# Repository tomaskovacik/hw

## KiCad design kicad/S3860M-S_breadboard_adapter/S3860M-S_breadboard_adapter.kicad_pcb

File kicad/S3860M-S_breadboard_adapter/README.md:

breadboard adapter for the S3860M-S module (check markings on your module, this is not for the XS3868 module, nor BLK module!)
 
What's new in version 2.0:

buttons: on/off, reset, next, previous, volume up and down

jack: output (optional over 1206 caps (by default this is bypassed by PCB trace, so trace need to be cut for caps to work), mono mic + all required bias circuit

12+12pin headers

breadboard adapters for these bluetooth modules can be purchase at Tindie.com :

BLK-MD-SPK-B https://www.tindie.com/products/tomaskovacik/breadboard-adapter-for-blk-md-spk-b/

XS3886 / S3860M-s https://www.tindie.com/products/tomaskovacik/breadboard-adapter-for-s3860m-s-sx3868/

SOYO-BT24G03 https://www.tindie.com/products/tomaskovacik/breadboard-adapter-for-soyo-bt24g03-bt-module/

F-3188 https://www.tindie.com/products/tomaskovacik/breadboard-adapter-for-f-3188-csr8645-module/

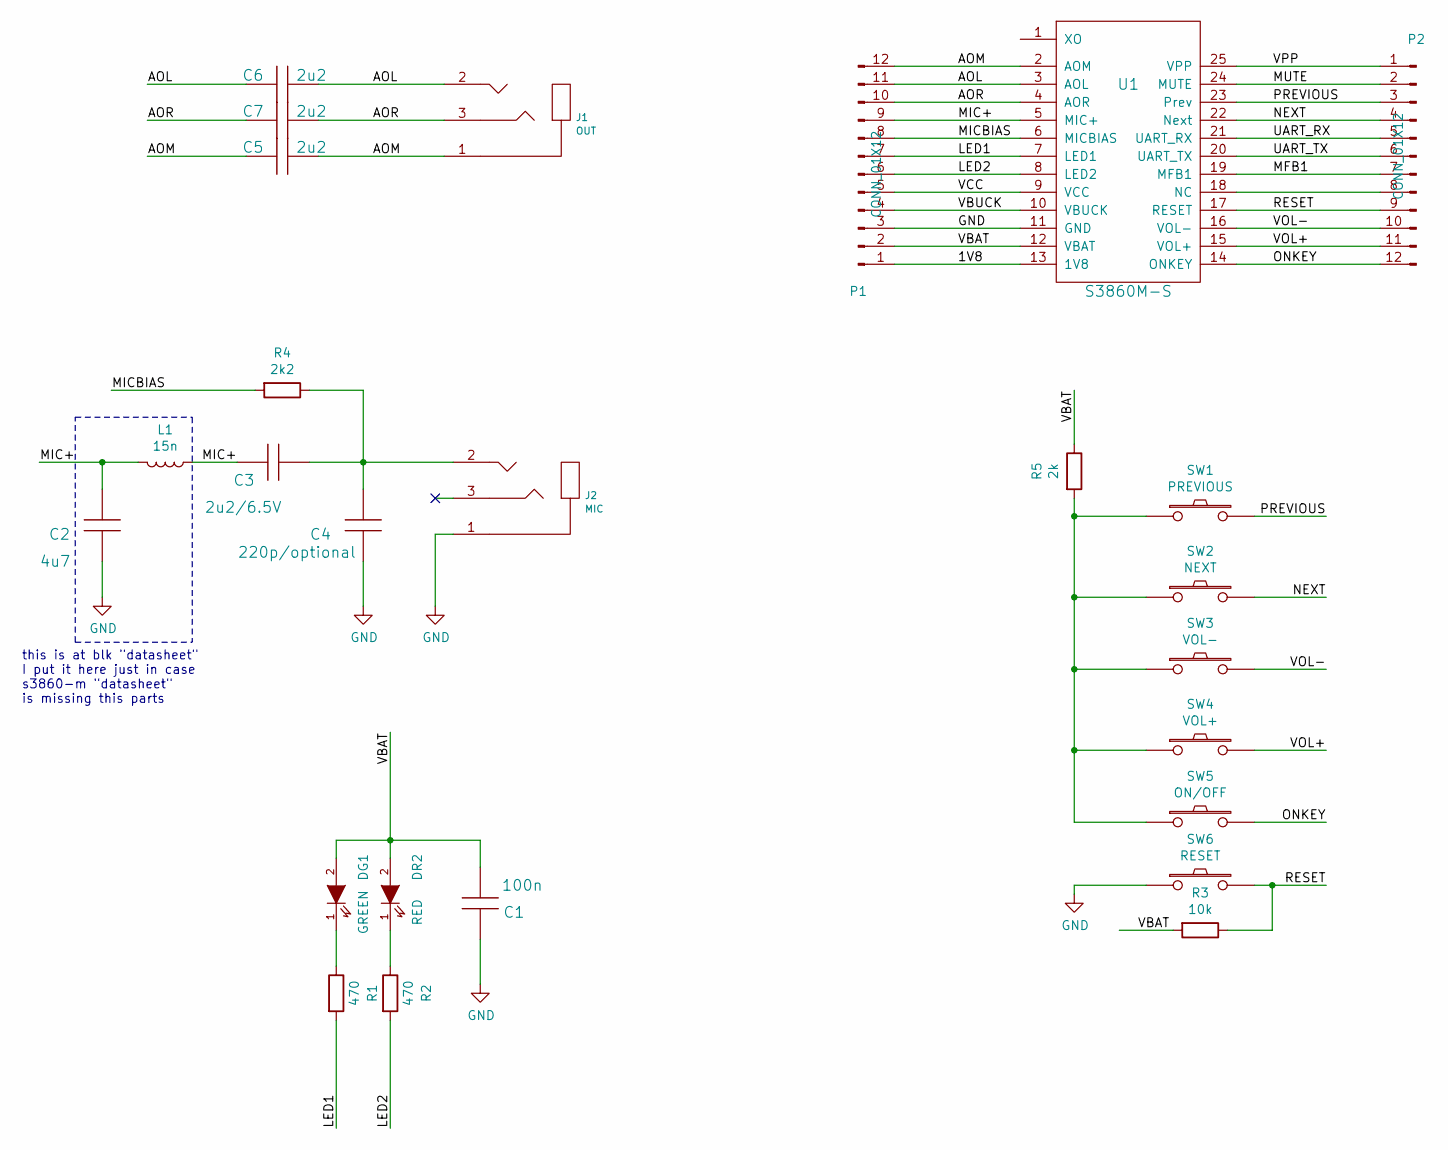
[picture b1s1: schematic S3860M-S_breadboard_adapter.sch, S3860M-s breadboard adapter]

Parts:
C1: 100n; C_0805_HandSoldering
C2: 4u7; C_1206_HandSoldering
C3: 2u2/6.5V; C_0805_HandSoldering
C4: 220p/optional; C_0805_HandSoldering
C5, C6, C7: 2u2; C_1206_HandSoldering
DG1: GREEN; LED-1206
DR2: RED; LED-1206
J1: OUT; 3.5mm_stereo_jack_PJ320B
J2: MIC; 3.5mm_stereo_jack_PJ320B
L1: 15n; Choke_SMD_1206_Handsoldering
P1, P2: CONN_01X12; Pin_Header_Straight_1x12_Pitch2.54mm
R1, R2: 470; R_0805_HandSoldering
R3: 10k; R_0805_HandSoldering
R4: 2k2; R_0805_HandSoldering
R5: 2k; R_0805_HandSoldering
SW1: PREVIOUS; SW_SPST_FSMSM
SW2: NEXT; SW_SPST_FSMSM
SW3: VOL-; SW_SPST_FSMSM
SW4: VOL+; SW_SPST_FSMSM
SW5: ON/OFF; SW_SPST_FSMSM
SW6: RESET; SW_SPST_FSMSM
U1: S3860M-S; XS3868

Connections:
/1V8: P1.1, U1.13 (1V8)
/AOL: C6.1, C6.2, J1.2, P1.11, U1.3 (AOL)
/AOM: C5.1, C5.2, J1.1, P1.12, U1.2 (AOM)
/AOR: C7.1, C7.2, J1.3, P1.10, U1.4 (AOR)
/LED1: P1.7, R1.2, U1.7 (LED1)
/LED2: P1.6, R2.2, U1.8 (LED2)
/MFB1: P2.7, U1.19 (MFB1)
/MIC+: C2.1, C3.1, L1.1, L1.2, P1.9, U1.5 (MIC+)
/MICBIAS: P1.8, R4.2, U1.6 (MICBIAS)
/MUTE: P2.2, U1.24 (MUTE)
/NEXT: P2.4, SW2.2, U1.22 (Next)
/ONKEY: P2.12, SW5.2, U1.14 (ONKEY)
/PREVIOUS: P2.3, SW1.2, U1.23 (Prev)
/RESET: P2.9, R3.1, SW6.2, U1.17 (RESET)
/UART_RX: P2.5, U1.21 (UART_RX)
/UART_TX: P2.6, U1.20 (UART_TX)
/VBAT: C1.2, DG1.2 (A), DR2.2 (A), P1.2, R3.2, R5.1, U1.12 (VBAT)
/VBUCK: P1.4, U1.10 (VBUCK)
/VCC: P1.5, U1.9 (VCC)
/VOL+: P2.11, SW4.2, U1.15 (VOL+)
/VOL-: P2.10, SW3.2, U1.16 (VOL-)
/VPP: P2.1, U1.25 (VPP)
GND: C1.1, C2.2, C4.2, J2.1, P1.3, SW6.1, U1.11 (GND)
unnamed: C3.2, C4.1, J2.2, R4.1
unnamed: DG1.1 (K), R1.1
unnamed: DR2.1 (K), R2.1
unnamed: P2.8, U1.18 (NC)
unnamed: R5.2, SW1.1, SW2.1, SW3.1, SW4.1, SW5.1

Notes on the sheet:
this is at blk "datasheet" I put it here just in case s3860-m "datasheet" is missing this parts

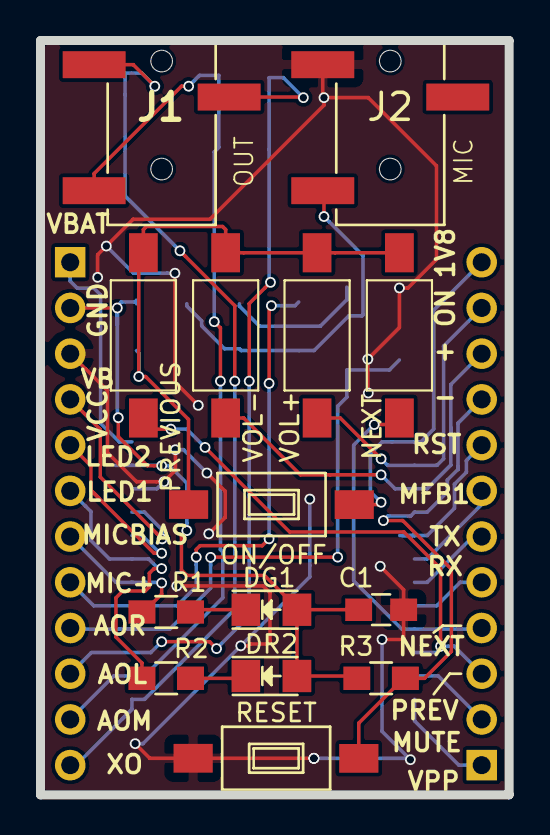
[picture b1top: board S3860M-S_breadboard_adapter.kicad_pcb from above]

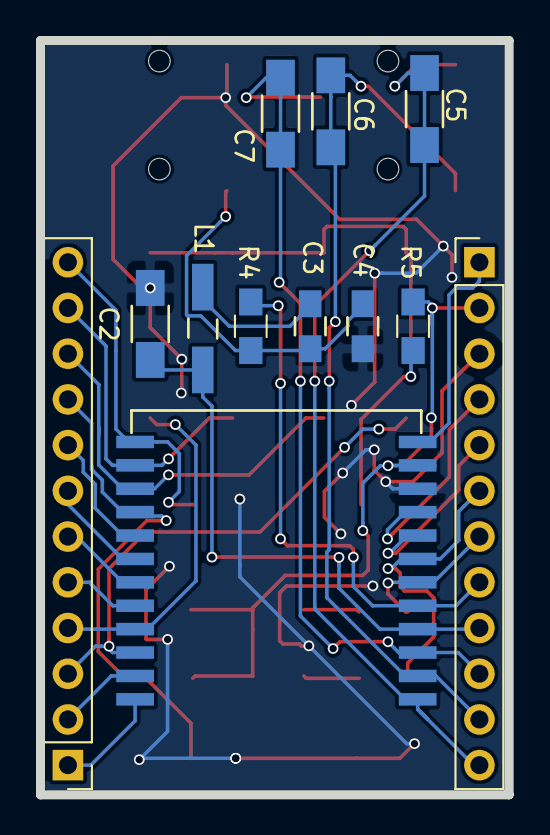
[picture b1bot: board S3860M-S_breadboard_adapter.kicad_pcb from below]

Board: 2 copper layers, 26.0 x 41.9 mm, 26 parts (12 on the bottom side), 28 nets.

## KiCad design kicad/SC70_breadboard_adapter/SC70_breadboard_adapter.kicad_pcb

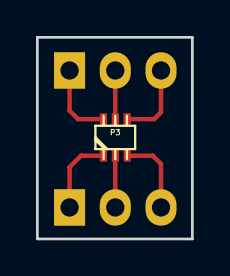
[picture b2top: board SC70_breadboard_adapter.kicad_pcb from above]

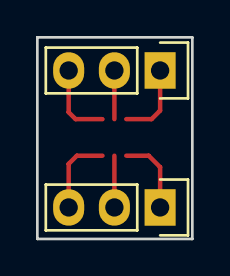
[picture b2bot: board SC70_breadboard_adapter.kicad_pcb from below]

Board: 2 copper layers, 8.6 x 11.2 mm, 3 parts (2 on the bottom side), 6 nets.

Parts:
P1, P2: CONN_01X03; Pin_Header_Straight_1x03
P3: DIL6; sc70-6

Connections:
unnamed: P1.1, P3.1
unnamed: P1.2, P3.2
unnamed: P1.3, P3.3
unnamed: P2.1, P3.6
unnamed: P2.2, P3.5
unnamed: P2.3, P3.4

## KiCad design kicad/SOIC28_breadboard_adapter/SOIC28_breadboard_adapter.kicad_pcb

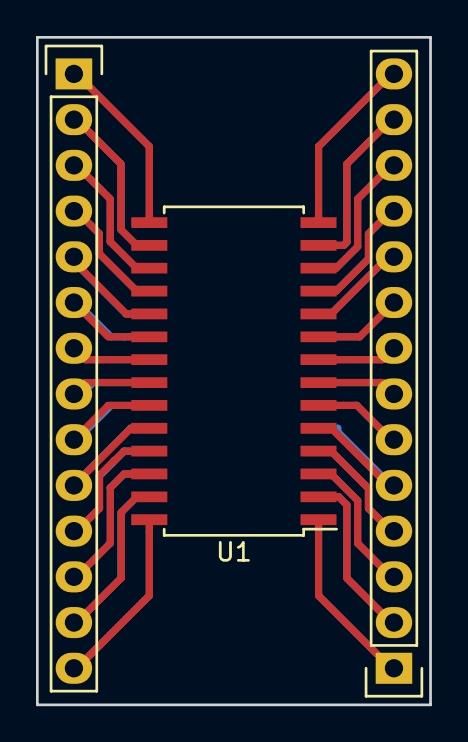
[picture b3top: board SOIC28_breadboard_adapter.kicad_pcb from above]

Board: 2 copper layers, 21.8 x 37.1 mm, 4 parts (1 on the bottom side), 24 nets.

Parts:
P1, P2: CONN_01X14; Pin_Header_Straight_1x14
U1, U2: HM62256BLFP-4SLT; SOIC-28_7.5x17.9mm_Pitch1.27mm

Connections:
GND: P1.1, P1.14, P2.1, P2.14, U1.1, U1.14, U1.15, U1.28, U2.1, U2.14, U2.15, U2.28
unnamed: P1.2, P2.5, U1.2, U1.19, U2.13, U2.24
unnamed: P1.3, U1.3, U2.12
unnamed: P1.4, U1.4, U2.11
unnamed: P1.5, U1.5, U2.10
unnamed: P1.6, U1.6, U2.9
unnamed: P1.7, U1.7, U2.8
unnamed: P1.8, U1.8, U2.7
unnamed: P1.9, U1.9, U2.6
unnamed: P1.10, U1.10, U2.5
unnamed: P1.11, U1.11, U2.4
unnamed: P1.12, U1.12, U2.3
unnamed: P1.13, U1.13, U2.2
unnamed: P2.2, U1.16, U2.27
unnamed: P2.3, U1.17, U2.26
unnamed: P2.4, U1.18, U2.25
unnamed: P2.6, U1.20, U2.23
unnamed: P2.7, U1.21, U2.22
unnamed: P2.8, U1.22, U2.21
unnamed: P2.9, U1.23, U2.20
unnamed: P2.10, U1.24, U2.19
unnamed: P2.11, U1.25, U2.18
unnamed: P2.12, U1.26, U2.17
unnamed: P2.13, U1.27, U2.16

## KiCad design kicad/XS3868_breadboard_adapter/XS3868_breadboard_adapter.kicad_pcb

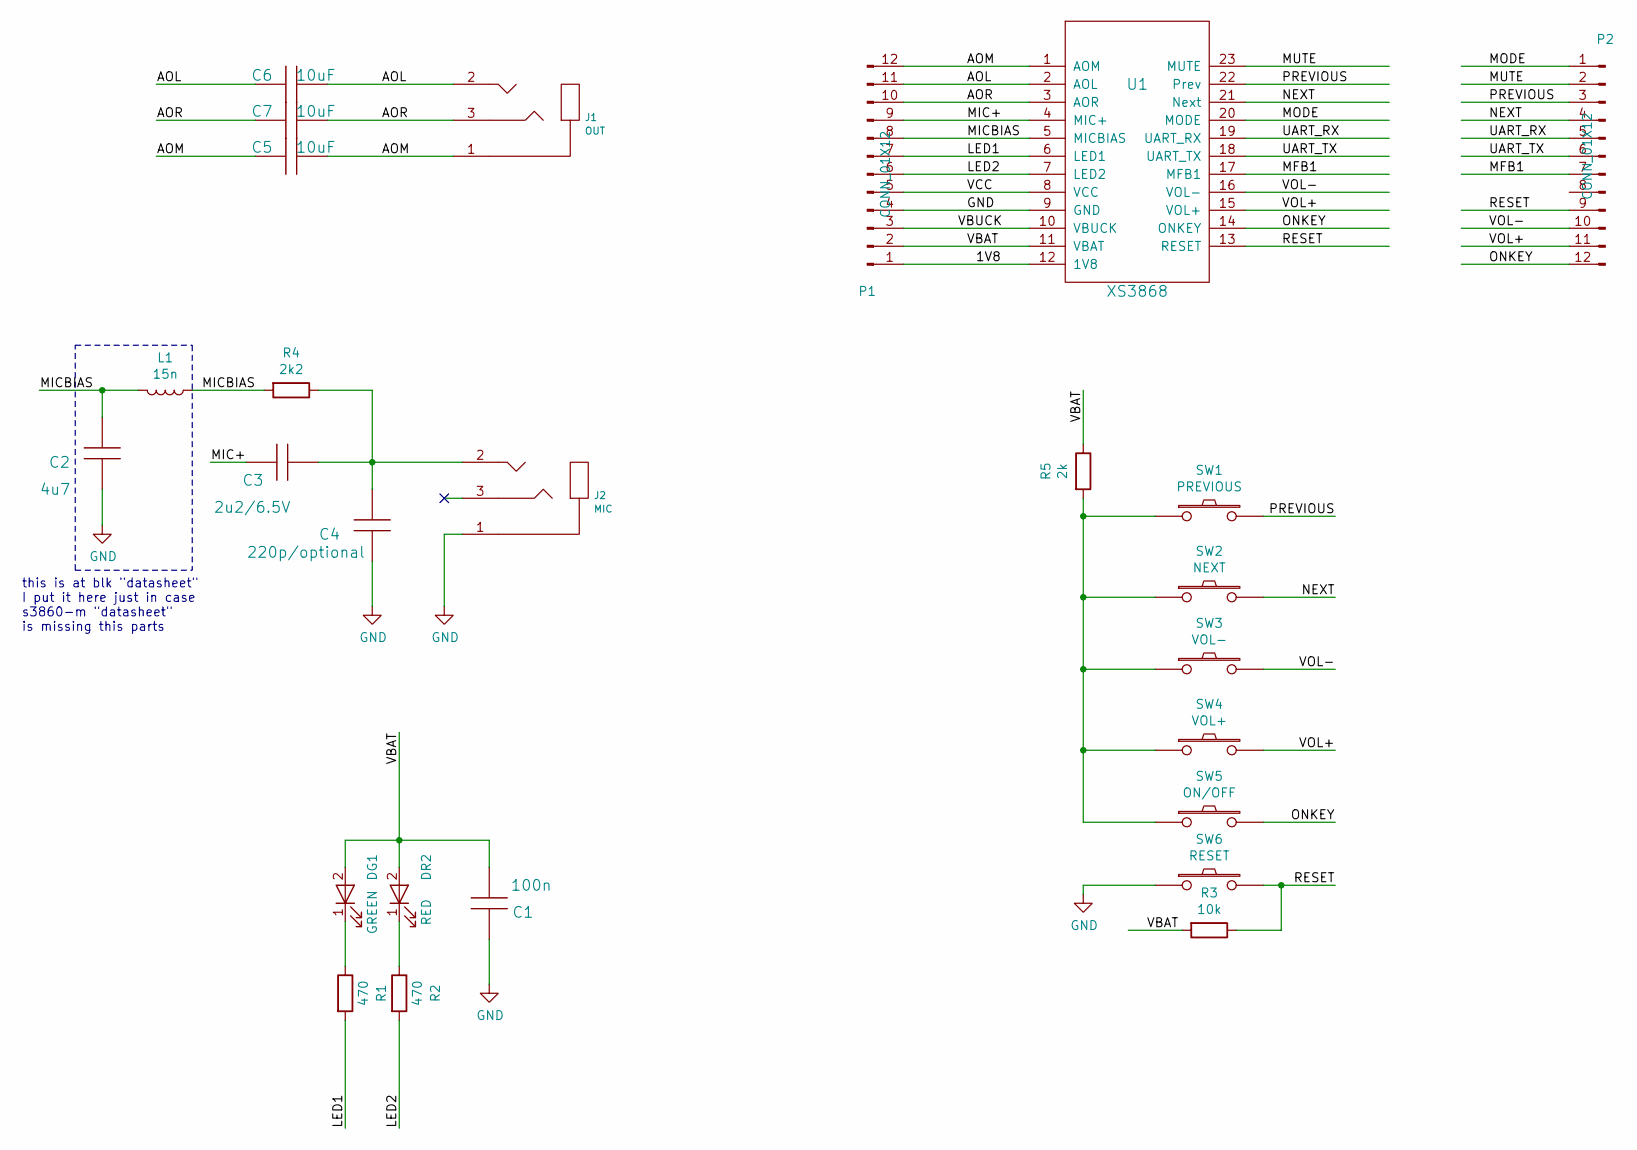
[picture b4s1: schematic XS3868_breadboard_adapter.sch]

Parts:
C1: 100n; C_0805_HandSoldering
C2: 4u7; C_1206_HandSoldering
C3: 2u2/6.5V; C_0805_HandSoldering
C4: 220p/optional; C_0805_HandSoldering
C5, C6, C7: 10uF; C_1206_HandSoldering
DG1: GREEN; LED-1206
DR2: RED; LED-1206
J1: OUT; 3.5mm_stereo_jack_PJ320B
J2: MIC; 3.5mm_stereo_jack_PJ320B
L1: 15n; Choke_SMD_1206_Handsoldering
P1, P2: CONN_01X12; Pin_Header_Straight_1x12_Pitch2.54mm
R1, R2: 470; R_0805_HandSoldering
R3: 10k; R_0805_HandSoldering
R4: 2k2; R_0805_HandSoldering
R5: 2k; R_0805_HandSoldering
SW1: PREVIOUS; SW_SPST_FSMSM
SW2: NEXT; SW_SPST_FSMSM
SW3: VOL-; SW_SPST_FSMSM
SW4: VOL+; SW_SPST_FSMSM
SW5: ON/OFF; SW_SPST_FSMSM
SW6: RESET; SW_SPST_FSMSM
U1: XS3868

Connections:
/1V8: P1.1, U1.12 (1V8)
/AOL: C6.1, C6.2, J1.2, P1.11, U1.2 (AOL)
/AOM: C5.1, C5.2, J1.1, P1.12, U1.1 (AOM)
/AOR: C7.1, C7.2, J1.3, P1.10, U1.3 (AOR)
/LED1: P1.7, R1.2, U1.6 (LED1)
/LED2: P1.6, R2.2, U1.7 (LED2)
/MFB1: P2.7, U1.17 (MFB1)
/MIC+: C3.1, P1.9, U1.4 (MIC+)
/MICBIAS: C2.1, L1.1, L1.2, P1.8, R4.2, U1.5 (MICBIAS)
/MODE: P2.1, U1.20 (MODE)
/MUTE: P2.2, U1.23 (MUTE)
/NEXT: P2.4, SW2.2, U1.21 (Next)
/ONKEY: P2.12, SW5.2, U1.14 (ONKEY)
/PREVIOUS: P2.3, SW1.2, U1.22 (Prev)
/RESET: P2.9, R3.1, SW6.2, U1.13 (RESET)
/UART_RX: P2.5, U1.19 (UART_RX)
/UART_TX: P2.6, U1.18 (UART_TX)
/VBAT: C1.2, DG1.2 (A), DR2.2 (A), P1.2, R3.2, R5.1, U1.11 (VBAT); also elsewhere on the board
/VBUCK: P1.3, U1.10 (VBUCK)
/VCC: P1.5, U1.8 (VCC)
/VOL+: P2.11, SW4.2, U1.15 (VOL+)
/VOL-: P2.10, SW3.2, U1.16 (VOL-)
GND: C1.1, C2.2, C4.2, J2.1, P1.4, SW6.1, U1.9 (GND)
unnamed: C3.2, C4.1, J2.2, R4.1
unnamed 24: DG1.1 (K), R1.1; also elsewhere on the board
unnamed 25: DR2.1 (K), R2.1; also elsewhere on the board
unnamed: R5.2, SW1.1, SW2.1, SW3.1, SW4.1, SW5.1

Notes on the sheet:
this is at blk "datasheet" I put it here just in case s3860-m "datasheet" is missing this parts

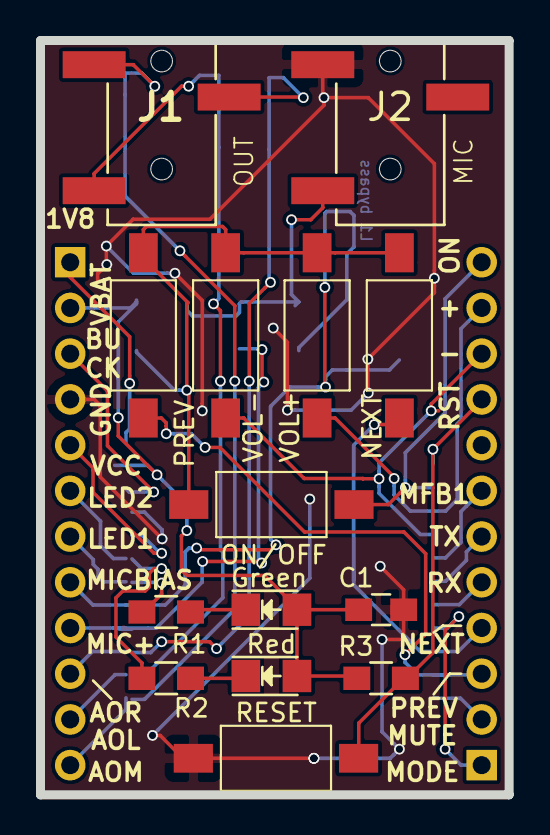
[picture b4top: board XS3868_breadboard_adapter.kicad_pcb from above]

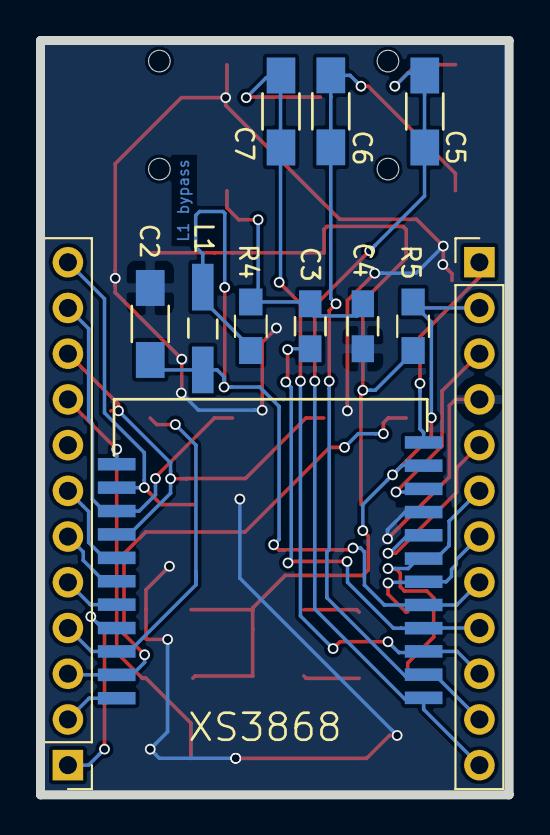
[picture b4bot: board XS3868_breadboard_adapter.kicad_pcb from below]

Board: 2 copper layers, 26.0 x 41.9 mm, 26 parts (12 on the bottom side), 27 nets.

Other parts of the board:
Green: GREEN; LED-1206
Red: RED; LED-1206

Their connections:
/VBAT: Green.2, Red.2; also elsewhere on the board
unnamed 24: Green.1; also elsewhere on the board
unnamed 25: Red.1; also elsewhere on the board

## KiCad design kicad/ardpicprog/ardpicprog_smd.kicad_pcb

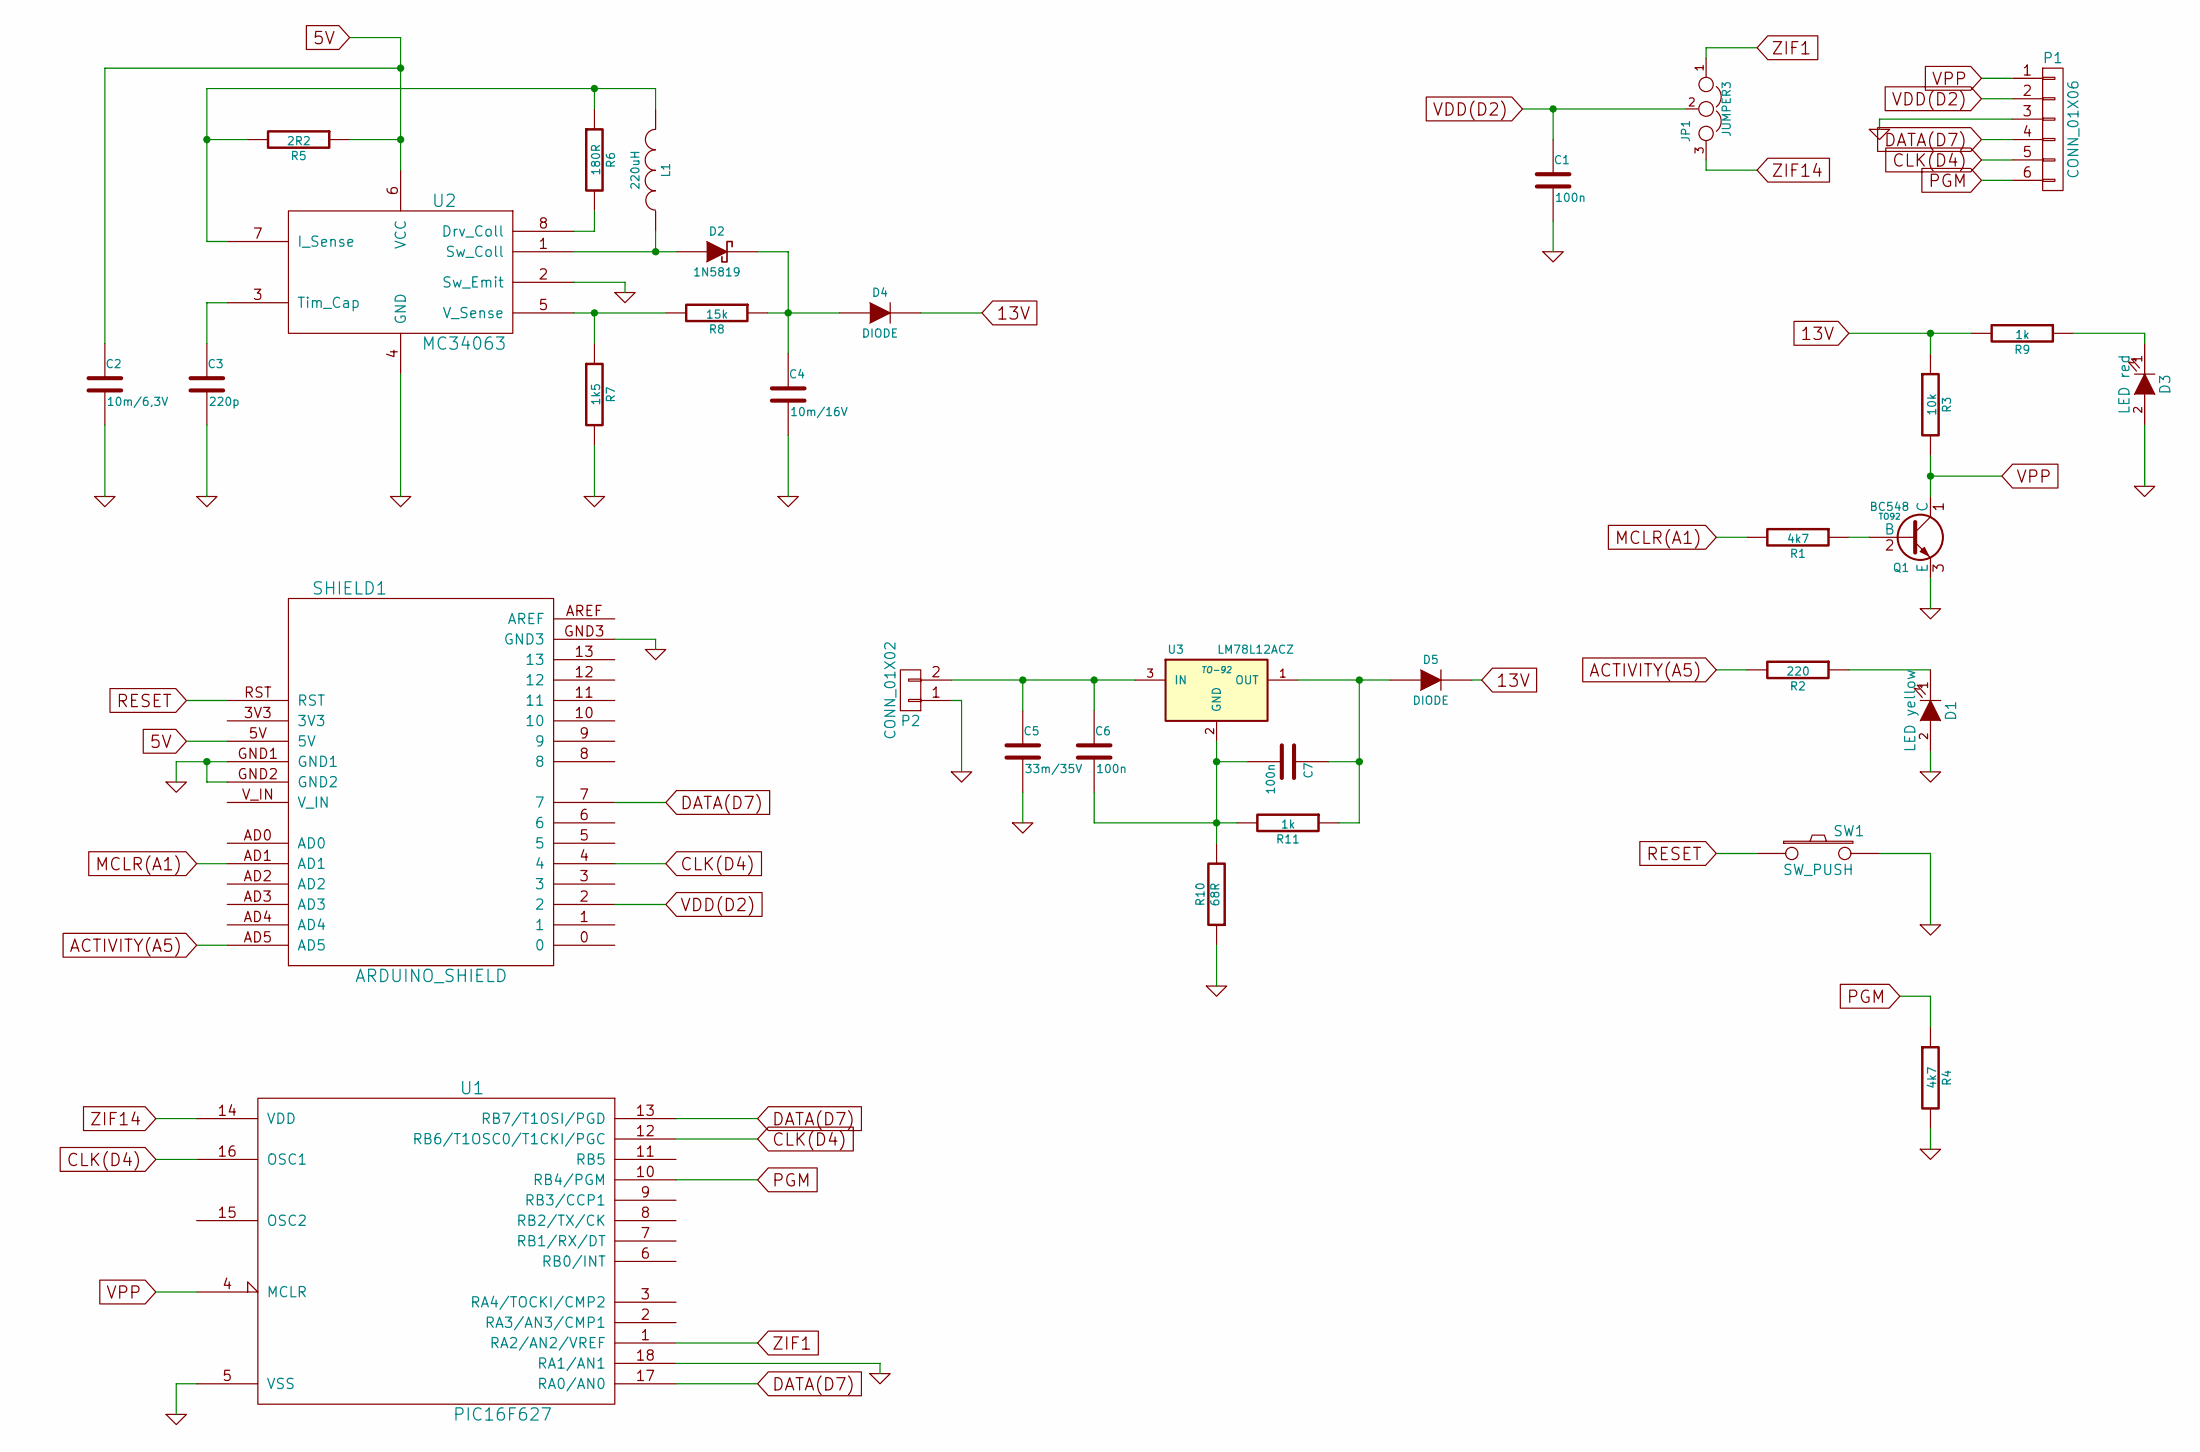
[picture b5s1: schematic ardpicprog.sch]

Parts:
C1, C6, C7: 100n
C2: 10m/6,3V
C3: 220p
C4: 10m/16V
C5: 33m/35V
D1: LED yellow
D2: 1N5819
D3: LED red
D4, D5: DIODE
JP1: JUMPER3
L1: 220uH
P1: CONN_01X06
P2: CONN_01X02
Q1: BC548; TO92
R1, R4: 4k7
R2: 220
R3: 10k
R5: 2R2
R6: 180R
R7: 1k5
R8: 15k
R9, R11: 1k
R10: 68R
SHIELD1: ARDUINO_SHIELD
SW1: SW_PUSH
U1: PIC16F627
U2: MC34063
U3: LM78L12ACZ; TO-92

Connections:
5V: C2.1, R5.1, SHIELD1.5V, U2.6 (VCC)
13V: D4.2 (K), D5.2 (K), R3.1, R9.2
ACTIVITY(A5): R2.2, SHIELD1.AD5
CLK(D4): P1.5, SHIELD1.4, U1.12 (RB6/T1OSC0/T1CKI/PGC), U1.16 (OSC1)
DATA(D7): P1.4, SHIELD1.7, U1.13 (RB7/T1OSI/PGD), U1.17 (RA0/AN0)
GND: C1.2, C2.2, C3.2, C4.2, C5.2, D1.2 (A), D3.2 (A), P1.3, P2.1, Q1.3 (E), R4.2, R7.2, R10.1, SHIELD1.GND1, SHIELD1.GND2, SHIELD1.GND3, SW1.2, U1.5 (VSS), U1.18 (RA1/AN1), U2.2 (Sw_Emit), U2.4 (GND)
MCLR(A1): R1.2, SHIELD1.AD1
unnamed: C3.1, U2.3 (Tim_Cap)
unnamed: C4.1, D2.2 (K), D4.1 (A), R8.1
unnamed: C5.1, C6.1, P2.2, U3.3 (IN)
unnamed: C6.2, C7.2, R10.2, R11.2, U3.2 (GND)
unnamed: C7.1, D5.1 (A), R11.1, U3.1 (OUT)
unnamed: D1.1 (K), R2.1
unnamed: D2.1 (A), L1.1, U2.1 (Sw_Coll)
unnamed: D3.1 (K), R9.1
unnamed: L1.2, R5.2, R6.1, U2.7 (I_Sense)
unnamed: Q1.2 (B), R1.1
unnamed: R6.2, U2.8 (Drv_Coll)
unnamed: R7.1, R8.2, U2.5 (V_Sense)
PGM: P1.6, R4.1, U1.10 (RB4/PGM)
RESET: SHIELD1.RST, SW1.1
VDD(D2): C1.1, JP1.2, P1.2, SHIELD1.2
VPP: P1.1, Q1.1 (C), R3.2, U1.4 (MCLR)
ZIF1: JP1.1, U1.1 (RA2/AN2/VREF)
ZIF14: JP1.3, U1.14 (VDD)

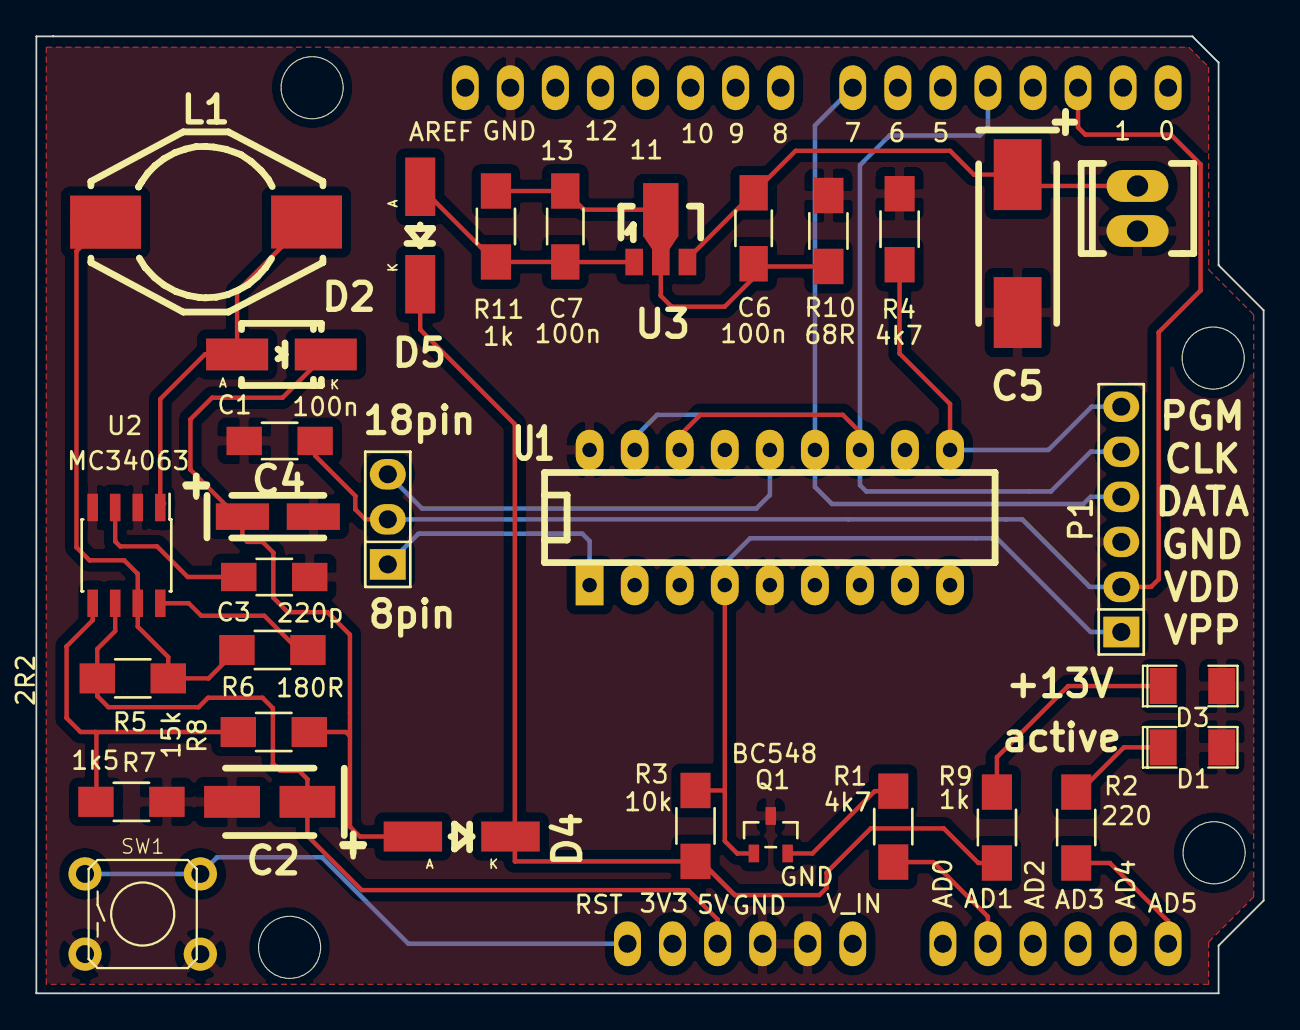
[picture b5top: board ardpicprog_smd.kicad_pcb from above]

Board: 2 copper layers, 69.2 x 53.9 mm, 37 parts (0 on the bottom side), 25 nets.

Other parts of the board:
MH: MountingHole_3-5mm_RevA_Date21Jun2010; MountingHole_3-5mm
MH#2, MH#3, MH#4: MountingHole_3-5mm_RevA_Date21Jun2010; MountingHole_3-5mm

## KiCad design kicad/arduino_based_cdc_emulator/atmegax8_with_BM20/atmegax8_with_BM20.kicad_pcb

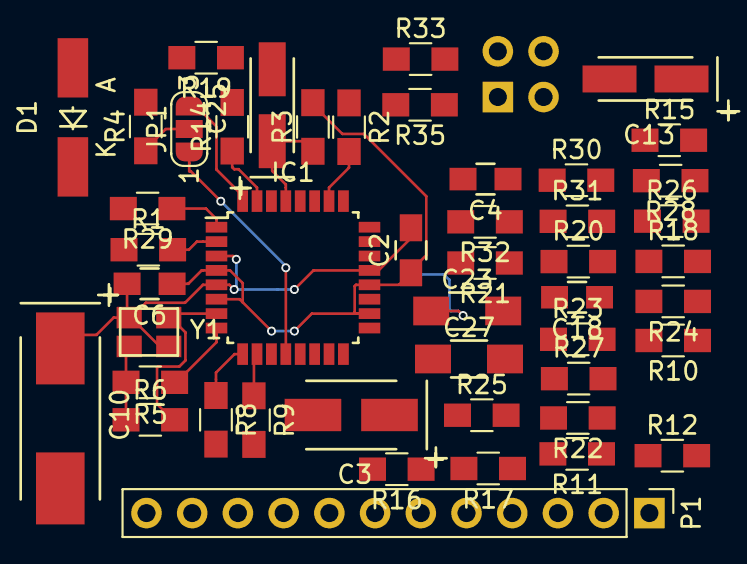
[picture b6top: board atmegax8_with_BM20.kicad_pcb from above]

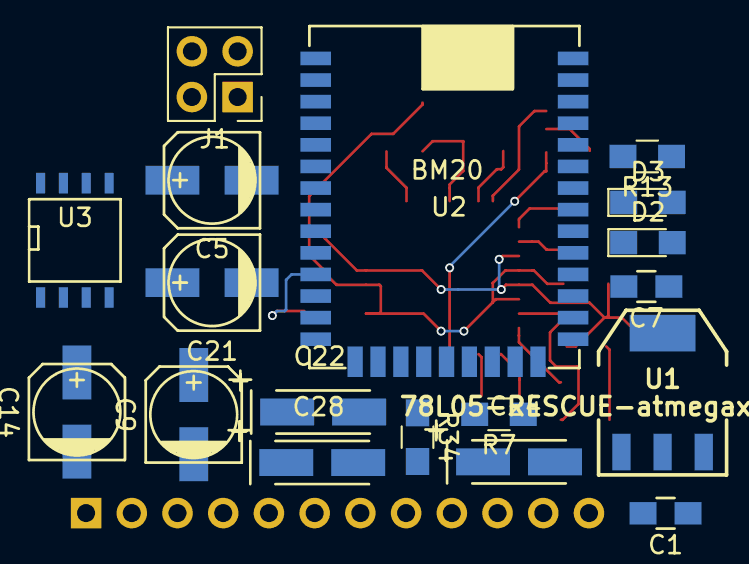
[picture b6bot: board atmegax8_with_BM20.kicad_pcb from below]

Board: 2 copper layers, 65 parts (18 on the bottom side), 53 nets.

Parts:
C1, C2, C6, C7: 100n; C_0805_HandSoldering
C3: 10m/16V; TantalC_SizeB_EIA-3528_HandSoldering
C4, C18: 10n; C_0805_HandSoldering
C5, C21: 4m7/16V; c_elec_5x5.8
C9: 47m/25V; c_elec_5x5.8
C10: CTS 47u/25V D 10% VIS-293D; TantalC_SizeD_EIA-7343_HandSoldering
C13: 2m2/16V; TantalC_SizeA_EIA-3216_HandSoldering
C14: 4u7/25V; c_elec_5x5.8
C22, C28: 2u2/16V; TantalC_SizeA_EIA-3216_HandSoldering
C23, C27: 1u/10V; C_1206_HandSoldering
C24, C25: 2u2; TantalC_SizeA_EIA-3216_HandSoldering
D1: 5V1; MiniMELF_Handsoldering
D2, D3: LED; LED_0805_HandSoldering
IC1: ATMEGA88-A; LQFP-32_7x7mm_Pitch0.8mm
J1: TEST_FLASH_MODE; Pin_Header_Straight_2x02_Pitch2.54mm
JP1: Jumper_3_Bridged12; SolderJumper-3_P1.3mm_Open_RoundedPad1.0x1.5mm_NumberLabels
P1: CONN_10; Pin_Header_Straight_1x12_Pitch2.54mm
R1, R2, R3, R4, R7: 3k3; R_0805_HandSoldering
R5: 27; R_0805_HandSoldering
R6: 1M; R_0805_HandSoldering
R8, R9, R13, R14: 330; R_0805_HandSoldering
R10, R11, R12, R16, R17, R24, R26, R28: 100k; R_0805_HandSoldering
R15, R18: 2M2; R_0805_HandSoldering
R19, R33, R34, R35: 4k7; R_0805_HandSoldering
R20, R31: 560; R_0805_HandSoldering
R21, R32: NP; R_0805_HandSoldering
R22, R27: 1k; R_0805_HandSoldering
R23, R30: 820; R_0805_HandSoldering
R25: 2k; R_0805_HandSoldering
R29: 10k; R_0805_HandSoldering
U1: 78L05-RESCUE-atmegax8_with_BM20; SOT-223-REGULATOR
U2: BM20
U3: LM358; SOIC-8-N
Y1: Crystal_GND24; crystal_FA238-TSX3225

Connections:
+5V: C2.1, C6.1, C7.1, IC1.4, IC1.6, IC1.18, IC1.20, R3.2, R7.2, U1.VO, U2.20
+12V: C1.1, C10.1, P1.7, R16.2, U1.VI, U3.8
/AOUTL: C14.2, P1.1, R12.2
/AOUTR: C9.2, P1.3, R11.2
/ARESET: C25.1, IC1.29, R3.1
/BTOUTL: C21.2, R21.2, U2.9
/BTOUTR: C5.2, R32.2, U2.7
/BT_RESET: C24.1, R7.1, R8.2, R34.1, U2.16
/CDC_ENA_5V: D1.1, IC1.1, R29.1
/CDC_ENA_12V: P1.11, R29.2
/Clock: IC1.2, R1.2
/DataIn: IC1.26, R2.2
/DataOut: P1.10, R4.2
/LED1: D2.1, U2.27
/LED2: D3.1, U2.28
/MFB: R9.2, U2.26
/MICN: C27.1, U2.12
/MICP: C23.1, U2.11
/MIC_BIAS: C22.1, R22.2, U2.13
/MIC_IN1: C27.2, P1.6, R25.2
/MIC_IN2: C23.2, P1.5, R27.1
/P2_0: J1.1, U2.4
/P2_4: J1.2, U2.36
/RX: R13.2, U2.32
/SYSPWR: D2.2, D3.2, U2.24
/TX: R14.2, R19.1, U2.33
/VGND: C13.1, R10.1, R16.1, R17.2, R24.1, R26.1, R28.1
GND: C1.2, C2.2, C3.2, C6.2, C7.2, C10.2, C13.2, C22.2, C24.2, C25.2, C28.2, D1.2, IC1.3, IC1.5, IC1.21, P1.8, R17.1, R19.2, R25.1, R33.1, R34.2, R35.2, U1.GND, U2.23, U2.37, Y1.3
GNDA: C4.2, C18.2, P1.2, P1.4, R11.1, R12.1, R20.1, R21.1, R31.1, R32.1, U2.8, U3.4
unnamed: C3.1, U2.10
unnamed: C4.1, R28.2, R30.2, U3.5
unnamed: C5.1, R30.1, R31.2
unnamed: C9.1, R15.2, U3.7
unnamed: C14.1, R18.2, U3.1
unnamed: C18.1, R23.2, R24.2, U3.3
unnamed: C21.1, R20.2, R23.1
unnamed: C28.1, R22.1, R27.2
unnamed: IC1.7, R6.1, Y1.2
unnamed: IC1.8, R5.2
unnamed: IC1.9, R8.1
unnamed: IC1.10, R9.1
unnamed: IC1.12, JP1.1
unnamed: IC1.30, R13.1
unnamed: IC1.31, R14.1
unnamed: IC1.32, JP1.3
unnamed: J1.3, R35.1
unnamed: J1.4, R33.2
unnamed: JP1.2, R4.1
unnamed: P1.9, R1.1
unnamed: P1.12, R2.1
unnamed: R5.1, R6.2, Y1.1
unnamed: R10.2, R18.1, U3.2
unnamed: R15.1, R26.2, U3.6

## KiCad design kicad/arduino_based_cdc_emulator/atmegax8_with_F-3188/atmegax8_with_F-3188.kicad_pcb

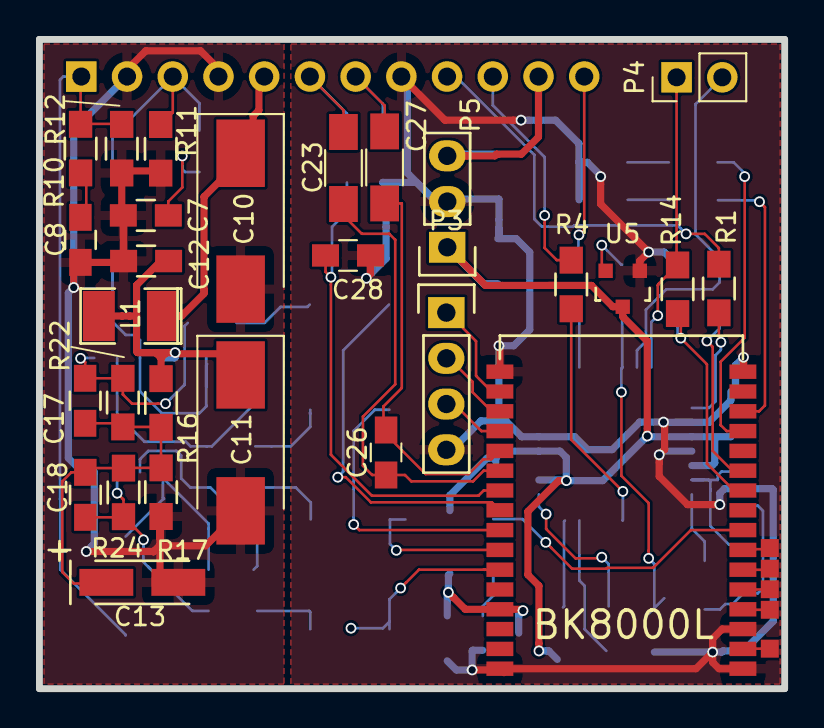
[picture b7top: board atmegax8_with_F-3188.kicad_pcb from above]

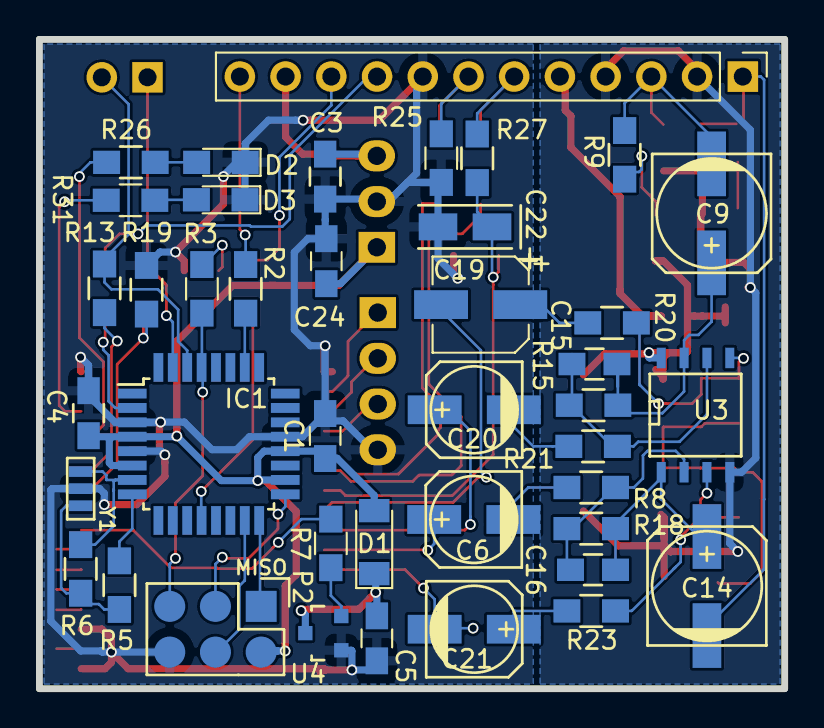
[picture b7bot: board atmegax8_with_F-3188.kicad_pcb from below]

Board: 2 copper layers, 41.4 x 36.1 mm, 74 parts (41 on the bottom side), 63 nets.

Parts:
C1, C3, C4, C5, C7, C8, C12, C24, C28: 100n; C_0805_HandSoldering
C6, C20, C21: 10m/16V; c_elec_5x5.8
C9, C14: 47m/25V; c_elec_6.3x5.7
C10: 100u/16V; CP_Tantalum_Case-D_EIA-7343-31_Hand
C11: 100m/16V; CP_Tantalum_Case-D_EIA-7343-31_Hand
C13: 2m2/16V; TantalC_SizeA_EIA-3216_HandSoldering
C15, C16, C17, C18: 33p; C_0805_HandSoldering
C19: 10m/16V; CP_Elec_5x5.8
C22: 4u7/10V; TantalC_SizeA_EIA-3216_Wave
C23, C27: 1u/10V; C_1206_HandSoldering
C26: 10n; C_0805_HandSoldering
D1: 1N4148; D_MiniMELF
D2, D3: LED; LED_0805_HandSoldering
IC1: ATMEGA88-A; TQFP-32_7x7mm_Pitch0.8mm
J1: Ant; 1pin_smd
J2: TMS; 1pin_smd
J3: TCK; 1pin_smd
J4: TDO; 1pin_smd
J5: TDI; 1pin_smd
L1: 330u; SMD-1210_Pol
P1: CONN_10; Pin_Header_Straight_1x12_Pitch2.54mm
P2: SPI; Pin_Header_Straight_2x03
P3: CONN_4; Pin_Header_Straight_1x04
P4: SERIAL; Pin_Header_Straight_1x02_Pitch2.54mm
P5: CONN_4; Pin_Header_Straight_1x03
R1, R2, R4: 3k3; R_0805_HandSoldering
R3, R7: 100; R_0805_HandSoldering
R5: 20; R_0805_HandSoldering
R6: 1M; R_0805_HandSoldering
R8, R20, R21, R23: 22k; R_0805_HandSoldering
R9, R10: 39R; R_0805_HandSoldering
R11, R12, R15, R18, R22, R24: 47k; R_0805_HandSoldering
R13, R14: 330; R_0805_HandSoldering
R16, R17: 100k; R_0805_HandSoldering
R19: 4k7; R_0805_HandSoldering
R25, R27: 1k2; R_0805_HandSoldering
R26, R31: 1k; R_0805_HandSoldering
U2: F-6188; F-6188_nosilk
U3: LM358; SOIC-8-N
U4, U5: MAX809; SOT-23
Y1: 16MHz; MURATA_CSTCE_V53

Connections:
+5V: C1.1, C4.1, C24.1, D1.2, IC1.4, IC1.6, IC1.18, IC1.20, P2.2, P5.1, U5.3
+12C: C11.1, C12.1, L1.2, R16.2, U3.8
+12V: C10.1, L1.1, P1.5
+BATT: C5.1, D1.1, U2.29, U4.3
/AOUTL: C14.2, P1.1, R10.2, R12.2
/AOUTR: C9.2, P1.3, R9.2, R11.2
/ARESET: IC1.29, P2.5, R3.2
/BTOUTL: C20.1, U2.25
/BTOUTLN: C19.2, U2.24
/BTOUTR: C6.1, U2.26
/BTOUTRN: C21.2, U2.27
/BT_RESET: R7.2, U2.8
/CDC_ENA_12V: C3.1, P1.11, P5.3
/Clock: IC1.2, R1.2
/DataIn: IC1.26, R2.2
/DataOut: P1.10, R4.2
/INL: P3.3, U2.20
/INR: P3.2, U2.19
/IN_DETECT: P3.1, U2.18
/LED1: R26.1, U2.13
/LED2: R31.1, U2.14
/MICN: C26.2, C27.1, U2.21
/MICP: C23.1, C26.1, U2.22
/MIC_BIAS: C22.1, C28.1, R27.2, U2.23
/MIC_IN1: C27.2, P1.7, R25.2
/MIC_IN2: C23.2, P1.6, R27.1
/MISO: IC1.16, P2.1
/MOSI: IC1.15, P2.4
/SCK: IC1.17, P2.3
/VGND: C13.1, C17.2, C18.2, R16.1, R17.2, R22.1, R24.1
GND: C1.2, C3.2, C4.2, C5.2, C22.2, C24.2, C28.2, D2.1, D3.1, IC1.3, IC1.5, IC1.21, P1.8, P2.6, P3.4, P5.2, R19.2, R25.1, U2.1, U2.3, U2.16, U2.17, U2.32, U4.1, U5.1, Y1.2
GNDA: C7.2, C8.2, C10.2, C11.2, C12.2, C13.2, P1.2, P1.4, R11.1, R12.1, R17.1, U3.4
unnamed: C6.2, R8.2
unnamed: C7.1, R9.1
unnamed: C8.1, R10.1
unnamed: C14.1, C16.1, R18.2, U3.1
unnamed: C9.1, C15.1, R15.2, U3.7
unnamed: C15.2, R15.1, R21.1, U3.6
unnamed: C16.2, R8.1, R18.1, U3.2
unnamed: C17.1, R20.2, R22.2, U3.5
unnamed: C18.1, R23.2, R24.2, U3.3
unnamed: C19.1, R20.1
unnamed: C20.2, R21.2
unnamed: C21.1, R23.1
unnamed: D2.2, R26.2
unnamed: D3.2, R31.2
unnamed: IC1.7, R6.1, Y1.3
unnamed: IC1.8, R5.2
unnamed: IC1.12, R4.1
unnamed: IC1.30, P4.2, R13.1
unnamed: IC1.31, P4.1, R14.1
unnamed: J1.1, U2.2
unnamed: J2.1, U2.4
unnamed: J3.1, U2.5
unnamed: J4.1, U2.6
unnamed: J5.1, U2.7
unnamed: P1.9, R1.1
unnamed: P1.12, R2.1
unnamed: R3.1, U5.2
unnamed: R5.1, R6.2, Y1.1
unnamed: R7.1, U4.2
RX: R13.2, U2.11
TX: R14.2, R19.1, U2.10
